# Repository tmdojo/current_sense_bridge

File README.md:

# Diode bridge rectifier and ADC break out board for clamp current sensors

This is designed for clamp current sensors such as:

TDK Corporation CCT261631-30-06-02
http://www.digikey.com/product-detail/en/tdk-corporation/CCT261631-30-06-02/445-172911-ND/5126210

The board is designed to fit nicely on Adafruit Feather line of products.
It also fit on Raspberry Pi although only ten pins are brokenout.
Mount it on a breadboard and you could combine it with many other microcontrollers such as Arduino Uno, MBED, etc

ADC part of the schematics and symbols are derived from the Adafruit 12 and 16 bit I2C ADC's with PGA.
https://github.com/adafruit/ADS1X15-Breakout-Board-PCBs

Please find the original readme text attached below.

----
This is the PCB for the Adafruit 12 and 16 bit I2C ADC's with PGA
Format is EagleCAD schematic and board layout

For more details, check out the product page at

-----> http://adafruit.com/products/1083
-----> http://adafruit.com/products/1085

Adafruit invests time and resources providing this open source design,
please support Adafruit and open-source hardware by purchasing
products from Adafruit!

Designed by Adafruit Industries.  
Creative Commons Attribution, Share-Alike license, check license.txt for more information
All text above must be included in any redistribution

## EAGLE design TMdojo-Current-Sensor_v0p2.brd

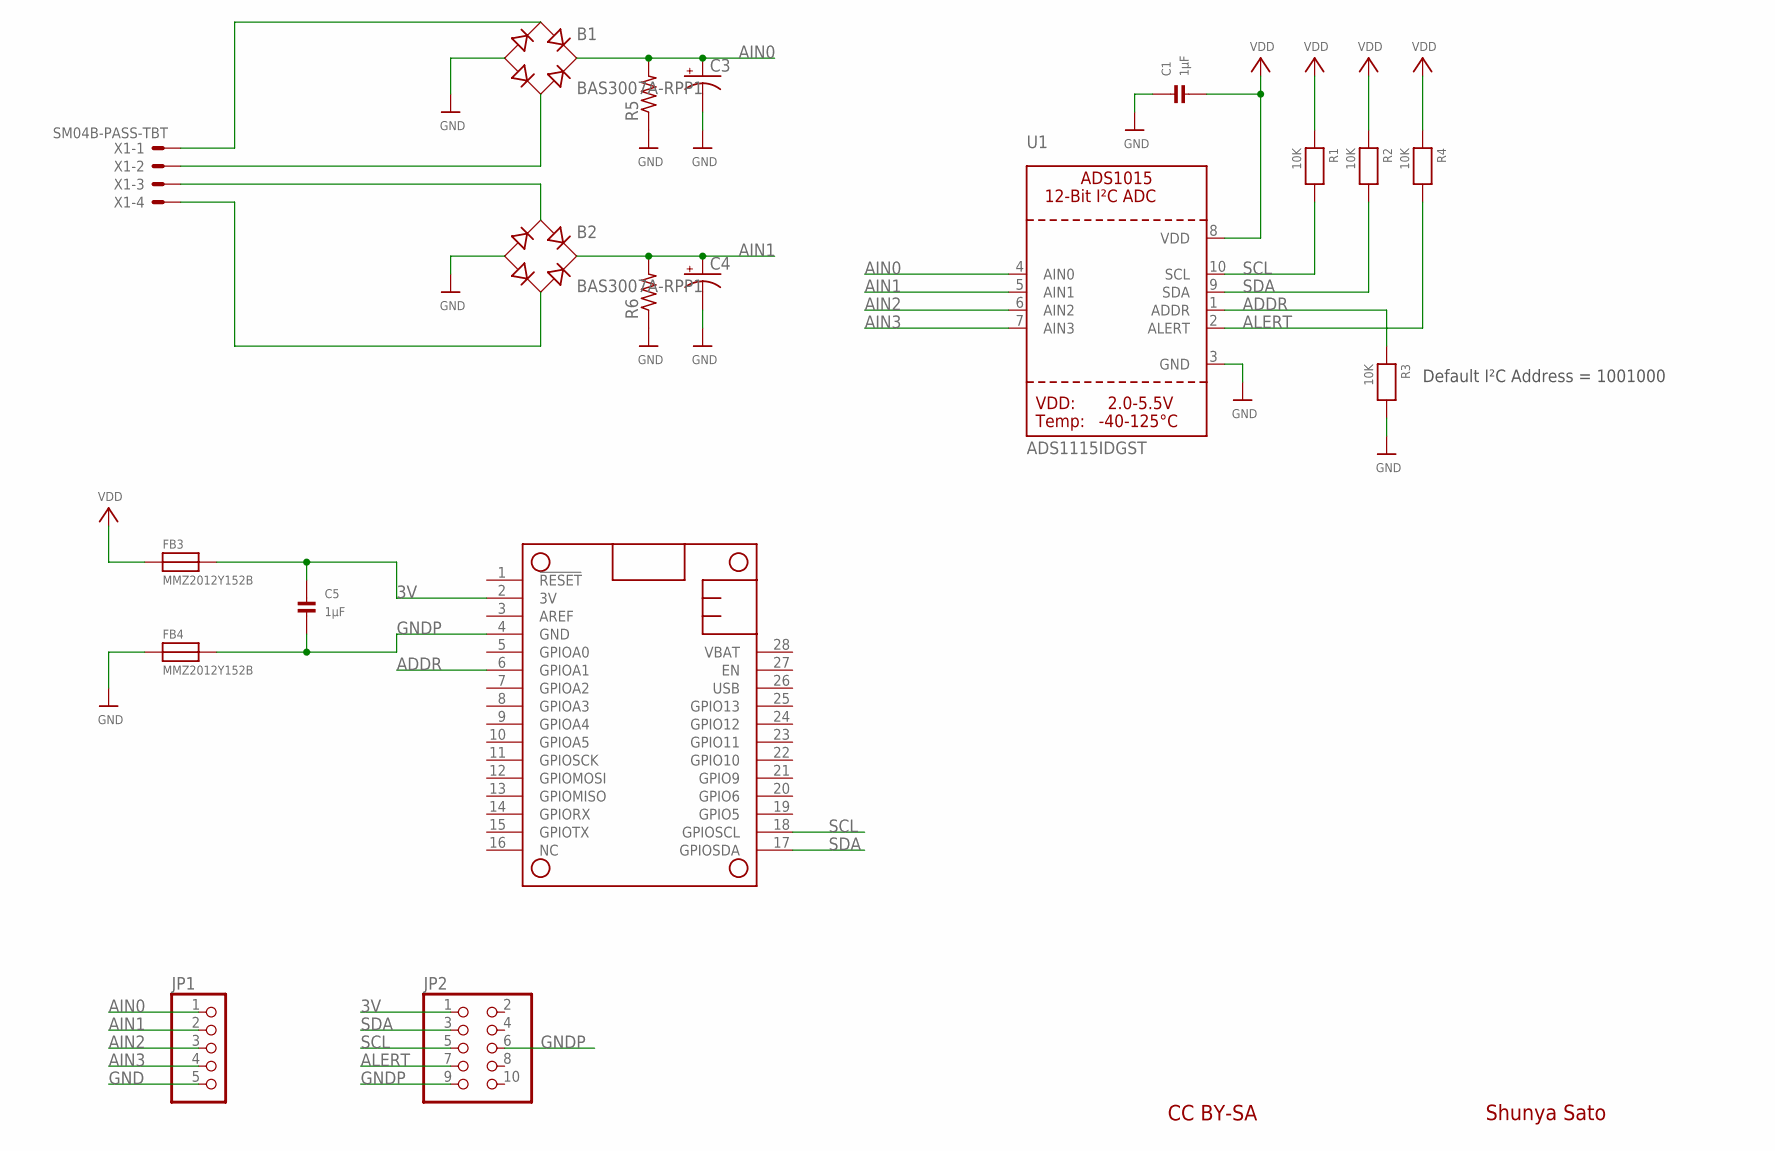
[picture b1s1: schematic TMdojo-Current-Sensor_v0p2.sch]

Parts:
B1, B2: BAS3007A-RPP1; SOT143
C1, C5: 1µF; 0805
C3, C4: CPOL-USTT5D7; TT5D7
FB3, FB4: MMZ2012Y152B; 0805
JP1: HEADER-1X5ROUND; 1X05_ROUND
JP2: HEADER-2X5; 2X05
MS1: FEATHERWING
R1, R2, R3, R4: 10K; 0805
R5, R6: R-US_FLIPFLOP; 0805-THM
U1: ADS1115IDGST; MSOP10
X1: SM04B-PASS-TBT

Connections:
3V: C5.1, FB3.2, JP2.1, MS1.2 (3V)
ADDR: MS1.6 (GPIOA1), R3.1, U1.1 (ADDR)
AIN0: B1.+, C3.+, JP1.1, R5.2, U1.4 (AIN0)
AIN1: B2.+, C4.+, JP1.2, R6.2, U1.5 (AIN1)
AIN2: JP1.3, U1.6 (AIN2)
AIN3: JP1.4, U1.7 (AIN3)
ALERT: JP2.7, R4.2, U1.2 (ALERT)
GND: B1.-, B2.-, C1.1, C3.-, C4.-, FB4.1, JP1.5, R3.2, R5.1, R6.1, U1.3 (GND)
GNDP: C5.2, FB4.2, JP2.6, JP2.9, MS1.4 (GND)
unnamed: B1.~1 (AC1), X1.1
unnamed: B1.~2 (AC2), X1.2
unnamed: B2.~1 (AC1), X1.3
unnamed: B2.~2 (AC2), X1.4
SCL: JP2.5, MS1.18 (GPIOSCL), R1.2, U1.10 (SCL)
SDA: JP2.3, MS1.17 (GPIOSDA), R2.2, U1.9 (SDA)
VDD: C1.2, FB3.1, R1.1, R2.1, R4.1, U1.8 (VDD)

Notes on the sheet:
Default I²C Address = 1001000
Shunya Sato
CC BY-SA

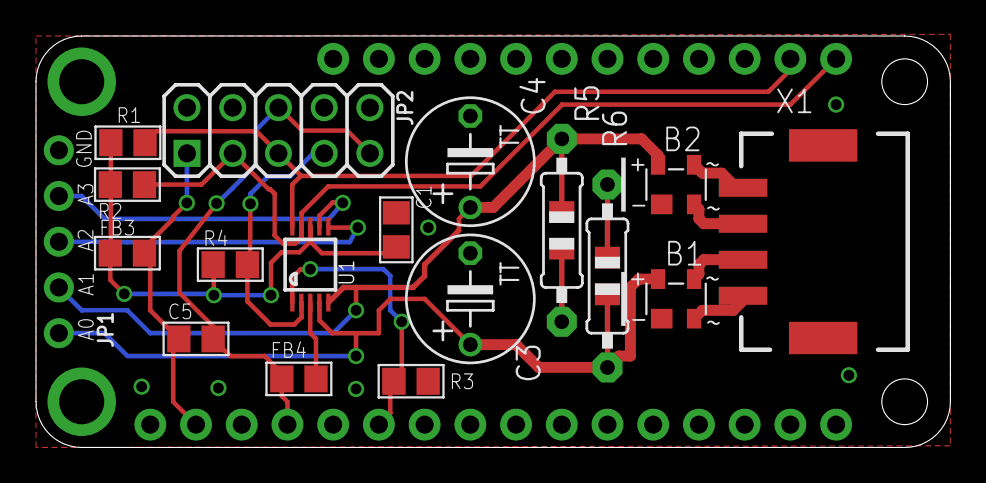
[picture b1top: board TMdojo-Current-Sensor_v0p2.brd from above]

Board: 2 copper layers, 50.8 x 22.9 mm, 19 parts (0 on the bottom side), 16 nets.

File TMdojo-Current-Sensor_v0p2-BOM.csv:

Part/Designator,Manufacture Part Number/Seeed SKU,Quantity,Digikey Part Number,Digikey Web Link,Note,,
U1,ADS1015IDGST,1,296-25227-1-ND,http://www.digikey.com/product-detail/en/texas-instruments/A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,,,
X2,SM04B-PASS-TBT(LF)(SN),1,455-2645-1-ND,http://www.digikey.com/product-detail/en/jst-sales-america-i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,,,
"B1, B2",BAS 3007A-RPP E6327,2,BAS3007A-RPPE6327INCT-ND,http://www.digikey.com/product-search/en/discrete-semiconduc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,,,
"C1, C5",CC0805KKX7R8BB105/302010179,2,311-1456-1-ND,http://www.digikey.com/product-search/en/capacitors/ceramic-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,1uF 0805,,
"R1, R2, R3, R4",RC0805FR-0710KL/301010361,4,311-10.0KCRCT-ND,http://www.digikey.com/product-search/en/resistors/chip-resi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,10k 0805,,
"FB3, FB4",MMZ2012Y152BT000,2,445-1560-1-ND,http://www.digikey.com/product-detail/en/tdk-corporation/MMZ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,FERRITE BEAD 1.5 KOHM 0805 1LN,,
"R5, R6",Non-Fit 300 Ohm,2,,,,,
"C3, C4",Non-Fit 220uF,2,493-6096-1-ND,https://www.digikey.jp/product-detail/ja/nichicon/UVR1C221ME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,7mmで220uFだと耐圧が16Vになっちゃう。25Vだと150uFが最大。経8mmだと220uFで25vある。,,
"JP1, JP2, MS1",Non-Fit,0,,,,,
,,,,,,,
,,,,,,,
,,,,,,,
,,,,,,,
,,,,,,,

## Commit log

2016-10-07 v0p2 is the first fabricated design.
2016-10-09 Add example Arduino sketch and BOM csv
2016-11-01 Add comment that it uses timer library
2017-05-01 Add websocket example for ESP8266. Add system diagram using AWS and MQTT.
2017-05-01 Add current monitor image for various coffee
